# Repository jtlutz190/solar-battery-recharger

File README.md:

# solar-battery-recharger
Designing and building a solar-powered battery recharger from the ground up, progressing from basic power regulation to battery charging, MPPT, and a custom PCB system.

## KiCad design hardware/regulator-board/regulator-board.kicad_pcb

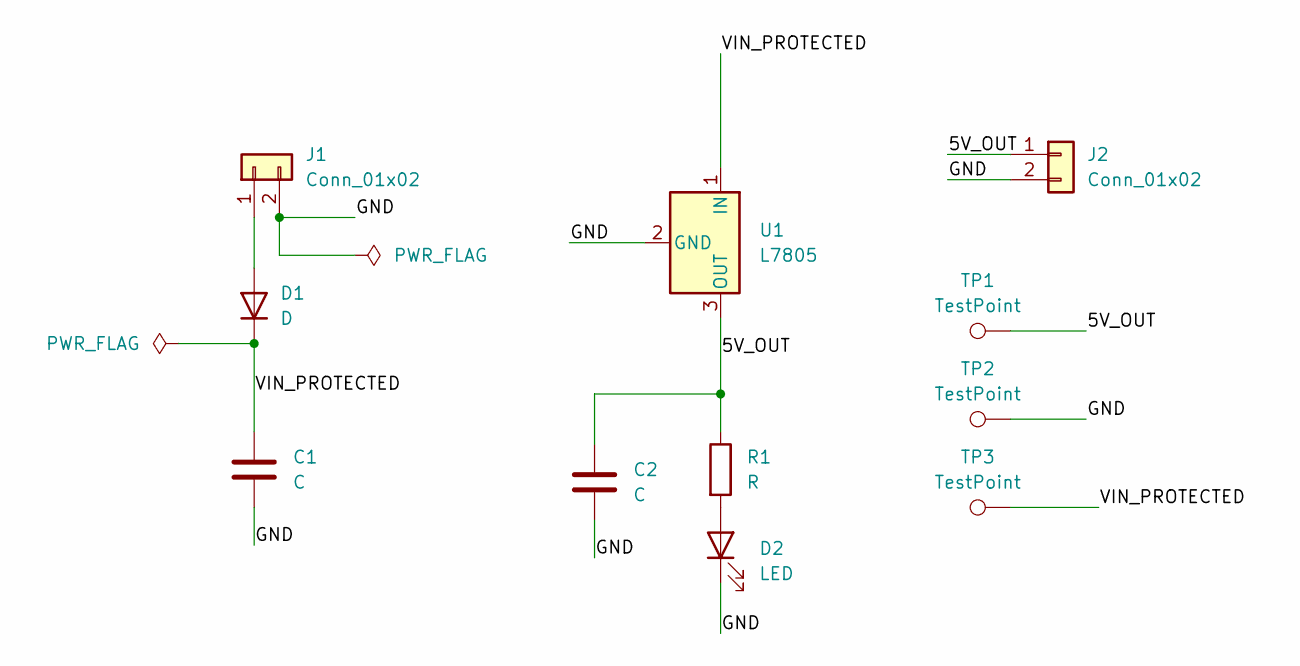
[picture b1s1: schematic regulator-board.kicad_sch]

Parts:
C1, C2: C; C_Disc_D5.0mm_W2.5mm_P5.00mm
D1: D; D_DO-41_SOD81_P10.16mm_Horizontal
D2: LED; LED_D5.0mm
J1, J2: Conn_01x02; TerminalBlock_CUI_TB007-508-02_1x02_P5.08mm_Horizontal
R1: R; R_Axial_DIN0207_L6.3mm_D2.5mm_P10.16mm_Horizontal
TP1, TP2, TP3: TestPoint; TestPoint_Loop_D2.50mm_Drill1.0mm
U1: L7805; TO-220-3_Vertical

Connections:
/5V_OUT: C2.1, J2.1, R1.1, TP1.1 (1_1), U1.3 (OUT)
/GND: C1.2, C2.2, D2.1 (K), J1.2, J2.2, TP2.1 (1_1), U1.2 (GND)
/VIN_PROTECTED: C1.1, D1.1 (K), TP3.1 (1_1), U1.1 (IN)
unnamed: D1.2 (A), J1.1
unnamed: D2.2 (A), R1.2

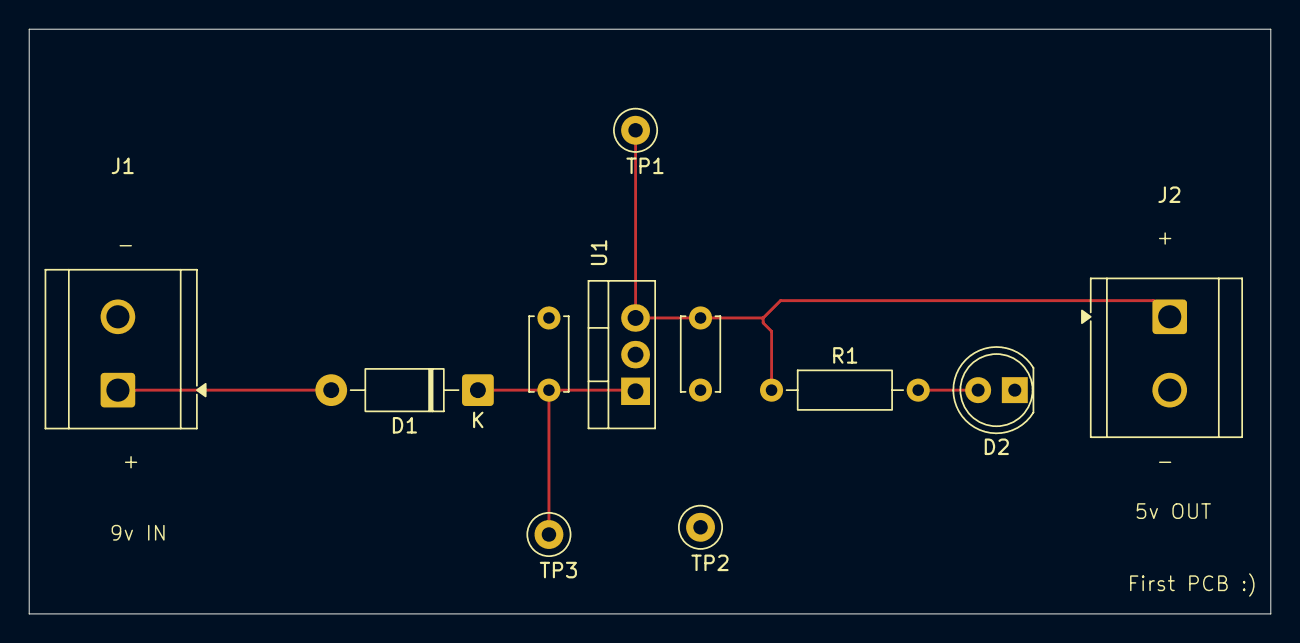
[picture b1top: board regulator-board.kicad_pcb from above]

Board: 2 copper layers, 86.0 x 40.5 mm, 11 parts (0 on the bottom side), 5 nets.
